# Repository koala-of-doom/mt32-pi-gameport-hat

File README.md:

# mt32-pi-gameport-hat

Raspberry Pi hat for [mt32-pi](https://github.com/dwhinham/mt32-pi) with the following features:
* 128x32 OLED display
* PCM5102 DAC
* 4 buttons
* MIDI input via DA-15 gameport
* Joystick passthrough

## Acknowledgments

Based on:
* [mt32-pi-midi-hat](https://github.com/chris-jh/mt32-pi-midi-hat)
* [clumsyMIDI](https://github.com/gmcn42/clumsyMIDI)

## License

This project is licensed under the [Creative Commons Attribution-ShareAlike 4.0 International License](https://creativecommons.org/licenses/by-sa/4.0/) - see the LICENSE.md file for details.

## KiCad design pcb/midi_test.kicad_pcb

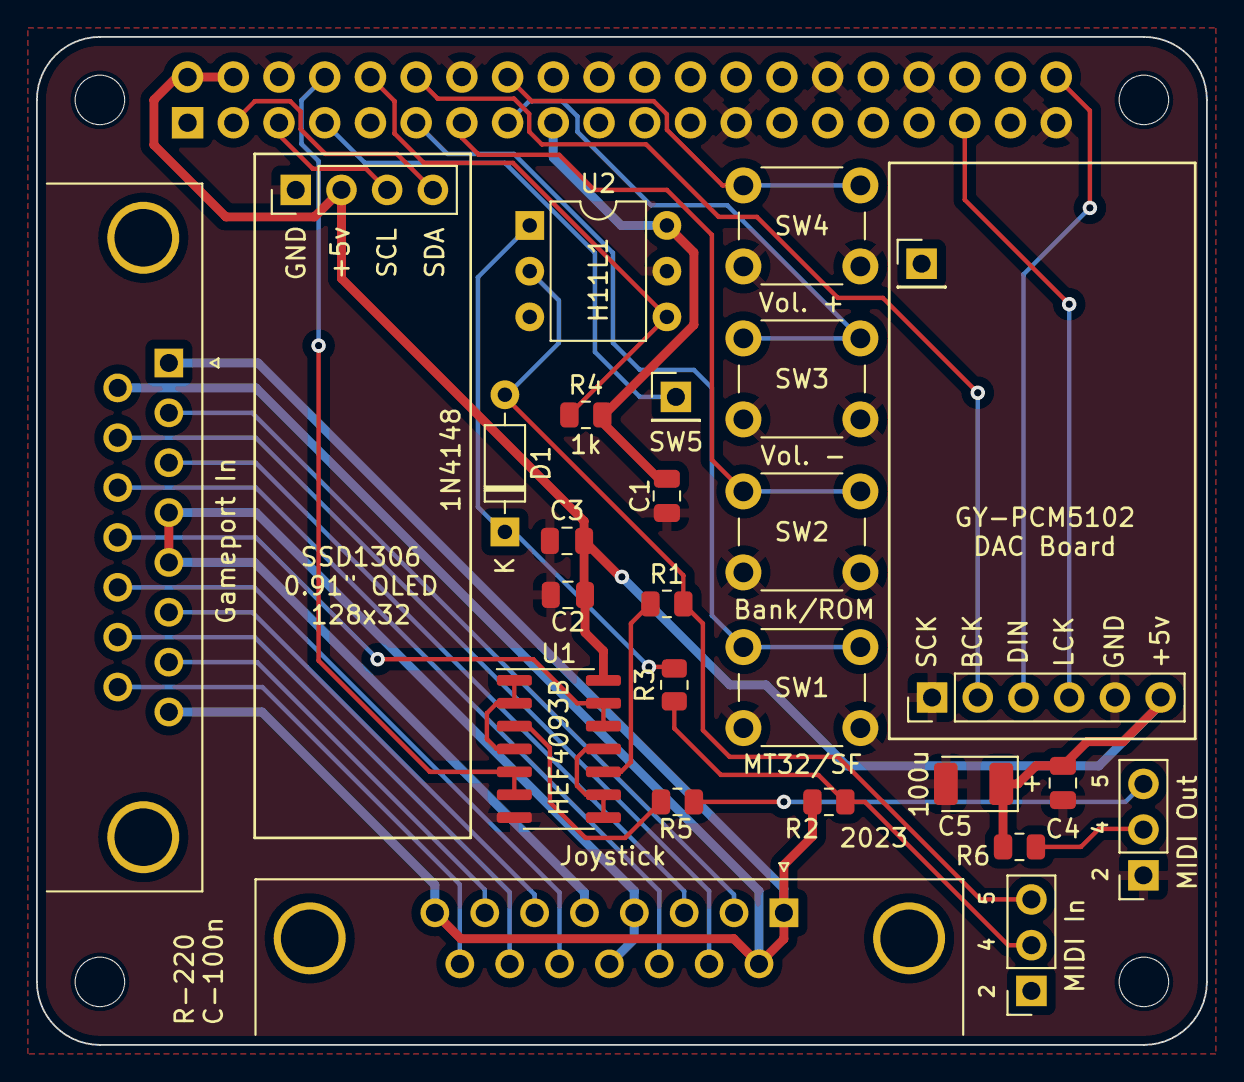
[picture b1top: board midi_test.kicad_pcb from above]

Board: 2 copper layers, 65.0 x 56.0 mm, 27 parts (0 on the bottom side), 36 nets.

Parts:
C1, C2, C3, C4: 100n; C_0805_2012Metric
C5: 100u; CP_EIA-3528-21_Kemet-B
D1: 1N4148; D_DO-35_SOD27_P7.62mm_Horizontal
J1: DA15_Male; DSUB-15_Male_Horizontal_P2.77x2.84mm_EdgePinOffset7.70mm_Ho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
J2: DA15_Female; DSUB-15_Female_Horizontal_P2.77x2.84mm_EdgePinOffset7.70mm_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
J3: Raspberry_Pi_2_3; raspberrypi_2_3
J4: In Pi/Out PC; PinSocket_1x03_P2.54mm_Vertical
J5: Midi Out Pi; PinSocket_1x03_P2.54mm_Vertical
J6: SSD1306 Header; PinHeader_1x04_P2.54mm_Vertical
J7: GY-PCM5102; PinHeader_1x06_P2.54mm_Vertical
J8: POST; PinHeader_1x01_P2.54mm_Vertical
J9: Button 5; PinHeader_1x01_P2.54mm_Vertical
R1, R2, R3, R5, R6: 220; R_0805_2012Metric
R4: 1k; R_0805_2012Metric
SW1, SW2, SW3, SW4: SW_Push; SW_PUSH_6mm
U1: HEF4093B; SOIC-14_3.9x8.7mm_P1.27mm
U2: H11L1; DIP-6_W7.62mm

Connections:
+3.3V: C1.1, J3.17 (3V3), R4.2, U2.6
+5 volts: J1.1, J1.8, J1.9, J2.1, J2.8, J2.9, R2.1
+5V: C2.1, C3.2, C4.2, C5.1, J3.2 (5V), J3.4 (5V), J6.2, J7.6 (VIN), R6.2, U1.14 (VCC)
Button_1: J3.11 (GPIO17), SW1.1
Button_2: J3.13 (GPIO27), SW2.1
Button_3: J3.15 (GPIO22), SW3.1
Button_4: J3.16 (GPIO23), SW4.1
Button_5: J3.7 (GCLK0/GPIO4), J9.1
GND: C1.2, C2.2, C3.1, C4.1, C5.2, J3.6 (GND), J3.14 (GND), J3.20 (GND), J3.25 (GND), J3.30 (GND), J3.34 (GND), J3.39 (GND), J5.1, J6.1, J7.1 (SCK), J7.5 (GND), SW1.2, SW2.2, SW3.2, SW4.2, U1.7 (GND), U2.5
Ground: J1.4, J1.5, J2.4, J2.5, J2.12
I2C_SCL: J3.5 (SCL/GPIO3), J6.3
I2C_SDA: J3.3 (SDA/GPIO2), J6.4
I2S_BCLK: J3.12 (GPIO18/PWM0), J7.2 (BCK)
I2S_DATA: J3.40 (GPIO21/SCLK1), J7.3 (DIN)
I2S_LRCLK: J3.35 (GPIO19/MISO1), J7.4 (LCK)
Joystick A, Button 1: J1.2, J2.2
Joystick A, Button 2: J1.7, J2.7
Joystick A, X Axis: J1.3, J2.3
Joystick A, Y Axis: J1.6, J2.6
Joystick B, Button 1: J1.10, J2.10
Joystick B, Button 2: J1.14, J2.14
Joystick B, X Axis: J1.11 (P111), J2.11 (P111)
Joystick B, Y Axis: J1.13, J2.13
MIDI RxD (Receive): J1.15, J2.15
MIDI TxD (Transmit): J1.12, U1.12, U1.13
unnamed: D1.2 (A), J4.3, R1.2, U2.2
unnamed: D1.1 (K), R3.2, U2.1
unnamed: J3.10 (GPIO15/RXD), R4.1, U2.4
unnamed: J4.2, R2.2, R3.1
unnamed: J5.2, R6.1
unnamed: J5.3, R5.1
unnamed: R1.1, U1.10
unnamed: R5.2, U1.3
unnamed: U1.1, U1.2, U1.4
unnamed: U1.8, U1.9, U1.11
TX_TTL: J3.8 (GPIO14/TXD), U1.5, U1.6
